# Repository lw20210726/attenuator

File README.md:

# 6GHz attenuator
- 10W celling
- Pick-able tunable 10dB + 20dB fixed: so 0dB - 30dB
- Calculate script included

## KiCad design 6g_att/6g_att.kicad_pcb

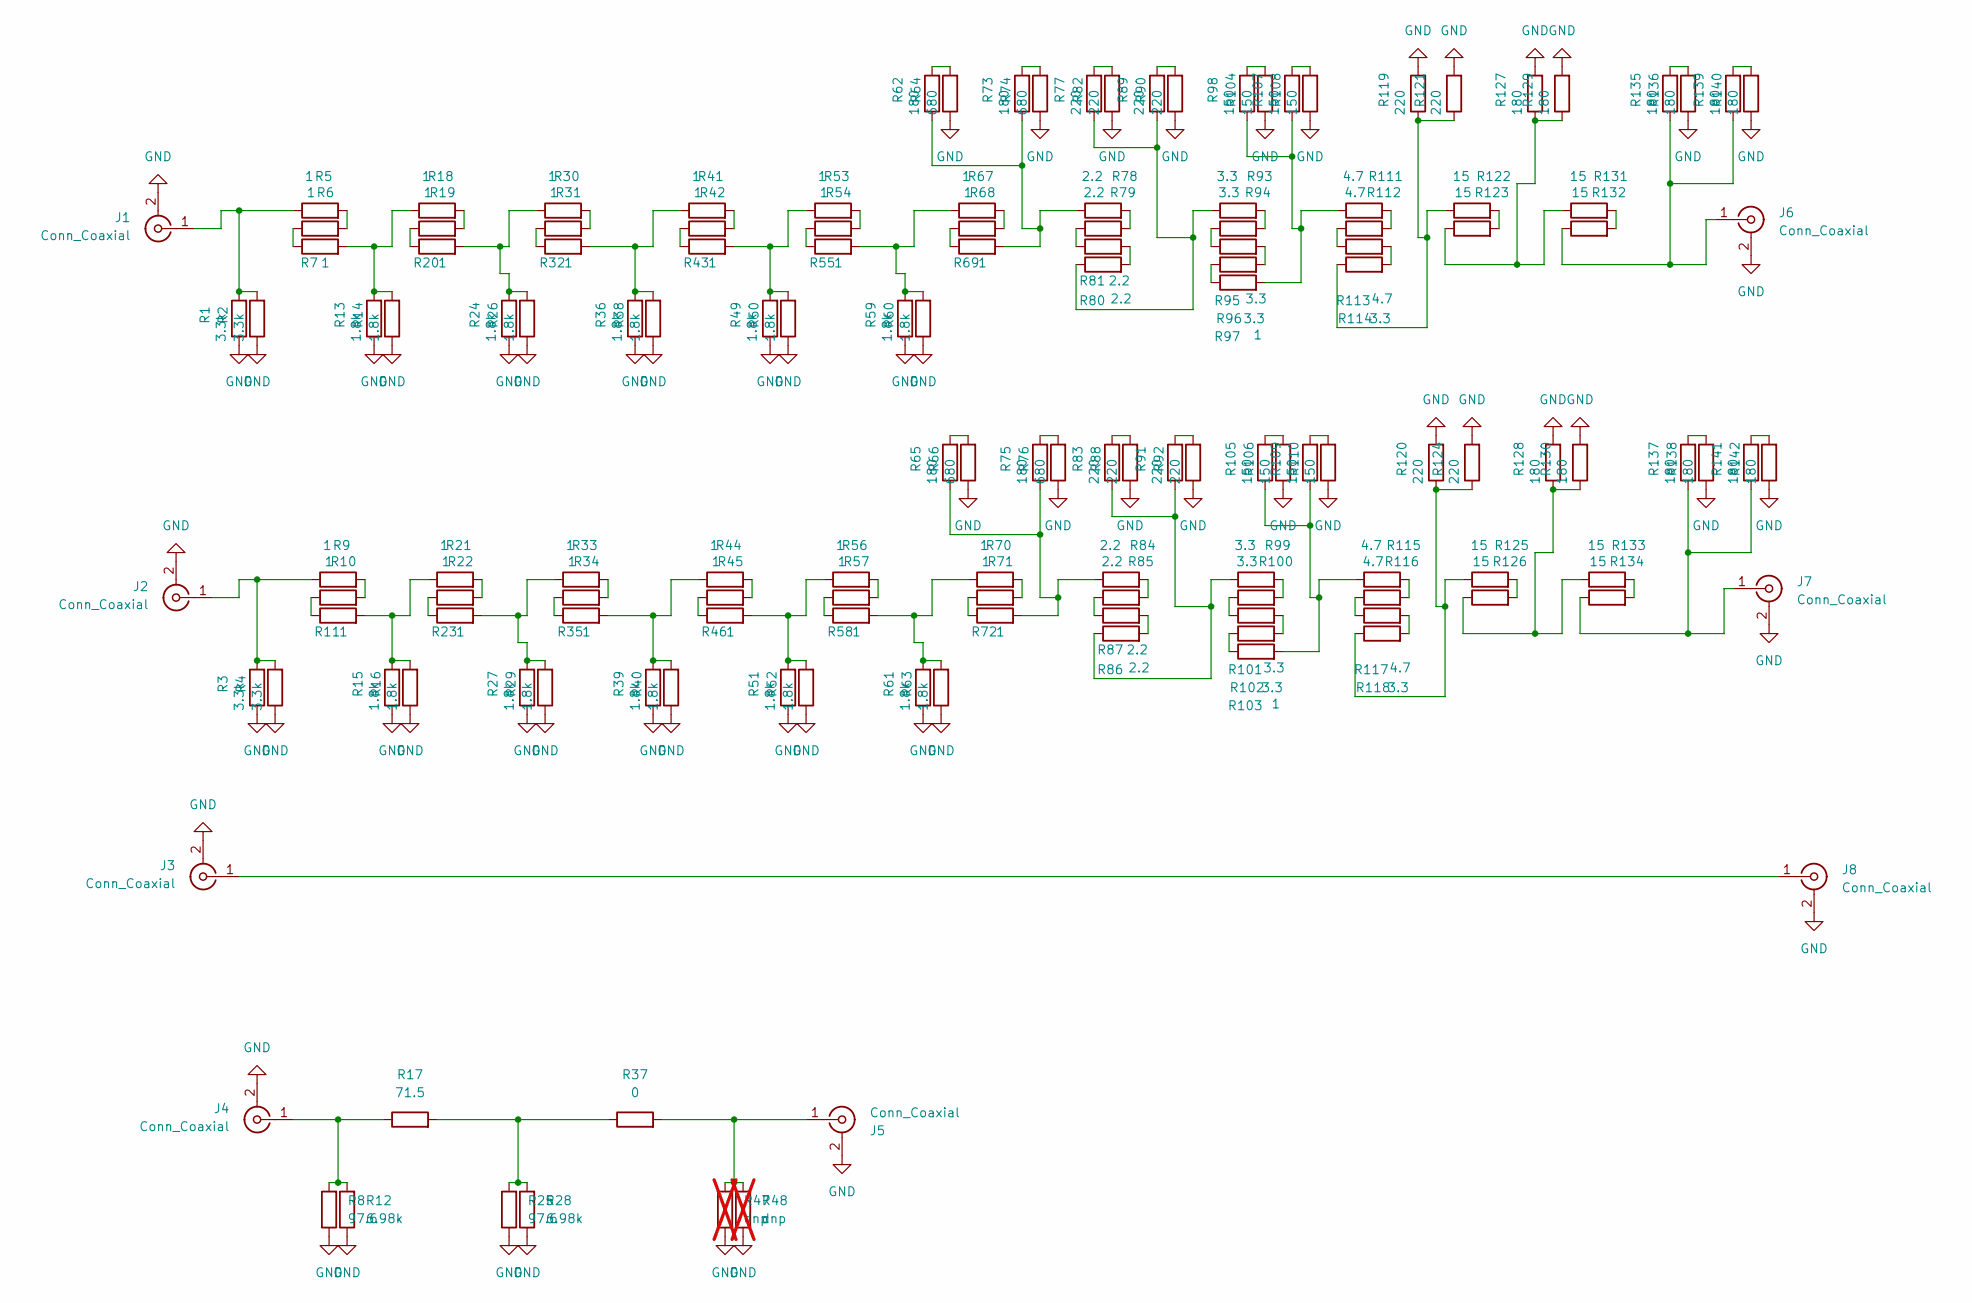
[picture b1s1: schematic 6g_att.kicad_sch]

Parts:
J1, J2, J3, J4, J5, J6, J7, J8: Conn_Coaxial; SMA_Samtec_SMA-J-P-H-ST-EM1_EdgeMount
R1, R2, R3, R4: 3.3k; R_0805_2012Metric
R5, R6, R7, R9, R10, R11, R18, R19, R20, R21, R22, R23, R30, R31, R32, R33, R34, R35, R41, R42, R43, R44, R45, R46, R53, R54, R55, R56, R57, R58, R67, R68, R69, R70, R71, R72, R97, R103: 1; R_0805_2012Metric
R8, R25: 97.6; R_0603_1608Metric
R12, R28: 6.98k; R_0603_1608Metric
R13, R14, R15, R16, R24, R26, R27, R29, R36, R38, R39, R40, R49, R50, R51, R52, R59, R60, R61, R63: 1.8k; R_0805_2012Metric
R17: 71.5; R_0603_1608Metric
R37: 0; R_0603_1608Metric
R47, R48: dnp; R_0603_1608Metric; not fitted
R62, R65, R73, R75, R127, R128, R129, R130, R135, R136, R137, R138, R139, R140, R141, R142: 180; R_0805_2012Metric
R64, R66, R74, R76: 680; R_0805_2012Metric
R77, R82, R83, R88, R89, R90, R91, R92, R119, R120, R121, R124: 220; R_0805_2012Metric
R78, R79, R80, R81, R84, R85, R86, R87: 2.2; R_0805_2012Metric
R93, R94, R95, R96, R99, R100, R101, R102, R114, R118: 3.3; R_0805_2012Metric
R98, R104, R105, R106, R107, R108, R109, R110: 150; R_0805_2012Metric
R111, R112, R113, R115, R116, R117: 4.7; R_0805_2012Metric
R122, R123, R125, R126, R131, R132, R133, R134: 15; R_0805_2012Metric

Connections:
GND: J1.2 (Ext), J2.2 (Ext), J3.2 (Ext), J4.2 (Ext), J5.2 (Ext), J6.2 (Ext), J7.2 (Ext), J8.2 (Ext), R1.1, R2.1, R3.1, R4.1, R8.1, R12.1, R13.1, R14.1, R15.1, R16.1, R24.1, R25.1, R26.1, R27.1, R28.1, R29.1, R36.1, R38.1, R39.1, R40.1, R47.1, R48.1, R49.1, R50.1, R51.1, R52.1, R59.1, R60.1, R61.1, R63.1, R64.1, R66.1, R74.1, R76.1, R82.1, R88.1, R90.1, R92.1, R104.1, R106.1, R108.1, R110.1, R119.2, R120.2, R121.2, R124.2, R127.2, R128.2, R129.2, R130.2, R136.1, R138.1, R140.1, R142.1
unnamed: J1.1 (In), R1.2, R2.2, R5.1
unnamed: J2.1 (In), R3.2, R4.2, R9.1
unnamed: J3.1 (In), J8.1 (In)
unnamed: J4.1 (In), R8.2, R12.2, R17.1
unnamed: J5.1 (In), R37.2, R47.2, R48.2
unnamed: J6.1 (In), R132.1, R135.1, R139.1
unnamed: J7.1 (In), R134.1, R137.1, R141.1
unnamed: R5.2, R6.2
unnamed: R6.1, R7.1
unnamed: R10.1, R11.1
unnamed: R9.2, R10.2
unnamed: R11.2, R15.2, R16.2, R21.1
unnamed: R7.2, R13.2, R14.2, R18.1
unnamed: R17.2, R25.2, R28.2, R37.1
unnamed: R18.2, R19.2
unnamed: R19.1, R20.1
unnamed: R20.2, R24.2, R26.2, R30.1
unnamed: R21.2, R22.2
unnamed: R22.1, R23.1
unnamed: R23.2, R27.2, R29.2, R33.1
unnamed: R30.2, R31.2
unnamed: R31.1, R32.1
unnamed: R32.2, R36.2, R38.2, R41.1
unnamed: R33.2, R34.2
unnamed: R34.1, R35.1
unnamed: R35.2, R39.2, R40.2, R44.1
unnamed: R41.2, R42.2
unnamed: R42.1, R43.1
unnamed: R43.2, R49.2, R50.2, R53.1
unnamed: R44.2, R45.2
unnamed: R45.1, R46.1
unnamed: R46.2, R51.2, R52.2, R56.1
unnamed: R53.2, R54.2
unnamed: R54.1, R55.1
unnamed: R55.2, R59.2, R60.2, R67.1
unnamed: R56.2, R57.2
unnamed: R57.1, R58.1
unnamed: R58.2, R61.2, R63.2, R70.1
unnamed: R62.1, R69.2, R73.1, R78.1
unnamed: R62.2, R64.2
unnamed: R65.1, R72.2, R75.1, R84.1
unnamed: R65.2, R66.2
unnamed: R67.2, R68.2
unnamed: R68.1, R69.1
unnamed: R70.2, R71.2
unnamed: R71.1, R72.1
unnamed: R73.2, R74.2
unnamed: R75.2, R76.2
unnamed: R77.1, R81.1, R89.1, R93.1
unnamed: R77.2, R82.2
unnamed: R78.2, R79.2
unnamed: R79.1, R80.1
unnamed: R80.2, R81.2
unnamed: R83.1, R87.1, R91.1, R99.1
unnamed: R83.2, R88.2
unnamed: R84.2, R85.2
unnamed: R85.1, R86.1
unnamed: R86.2, R87.2
unnamed: R89.2, R90.2
unnamed: R91.2, R92.2
unnamed: R93.2, R94.2
unnamed: R94.1, R95.1
unnamed: R95.2, R96.2
unnamed: R96.1, R97.1
unnamed: R100.1, R101.1
unnamed: R99.2, R100.2
unnamed: R101.2, R102.2
unnamed: R102.1, R103.1
unnamed: R103.2, R105.1, R109.1, R115.1
unnamed: R98.2, R104.2
unnamed: R105.2, R106.2
unnamed: R97.2, R98.1, R107.1, R111.1
unnamed: R107.2, R108.2
unnamed: R109.2, R110.2
unnamed: R111.2, R112.2
unnamed: R112.1, R113.1
unnamed: R113.2, R114.2
unnamed: R114.1, R119.1, R121.1, R122.1
unnamed: R115.2, R116.2
unnamed: R116.1, R117.1
unnamed: R117.2, R118.2
unnamed: R118.1, R120.1, R124.1, R125.1
unnamed: R122.2, R123.2
unnamed: R123.1, R127.1, R129.1, R131.1
unnamed: R125.2, R126.2
unnamed: R126.1, R128.1, R130.1, R133.1
unnamed: R131.2, R132.2
unnamed: R133.2, R134.2
unnamed: R135.2, R136.2
unnamed: R137.2, R138.2
unnamed: R139.2, R140.2
unnamed: R141.2, R142.2

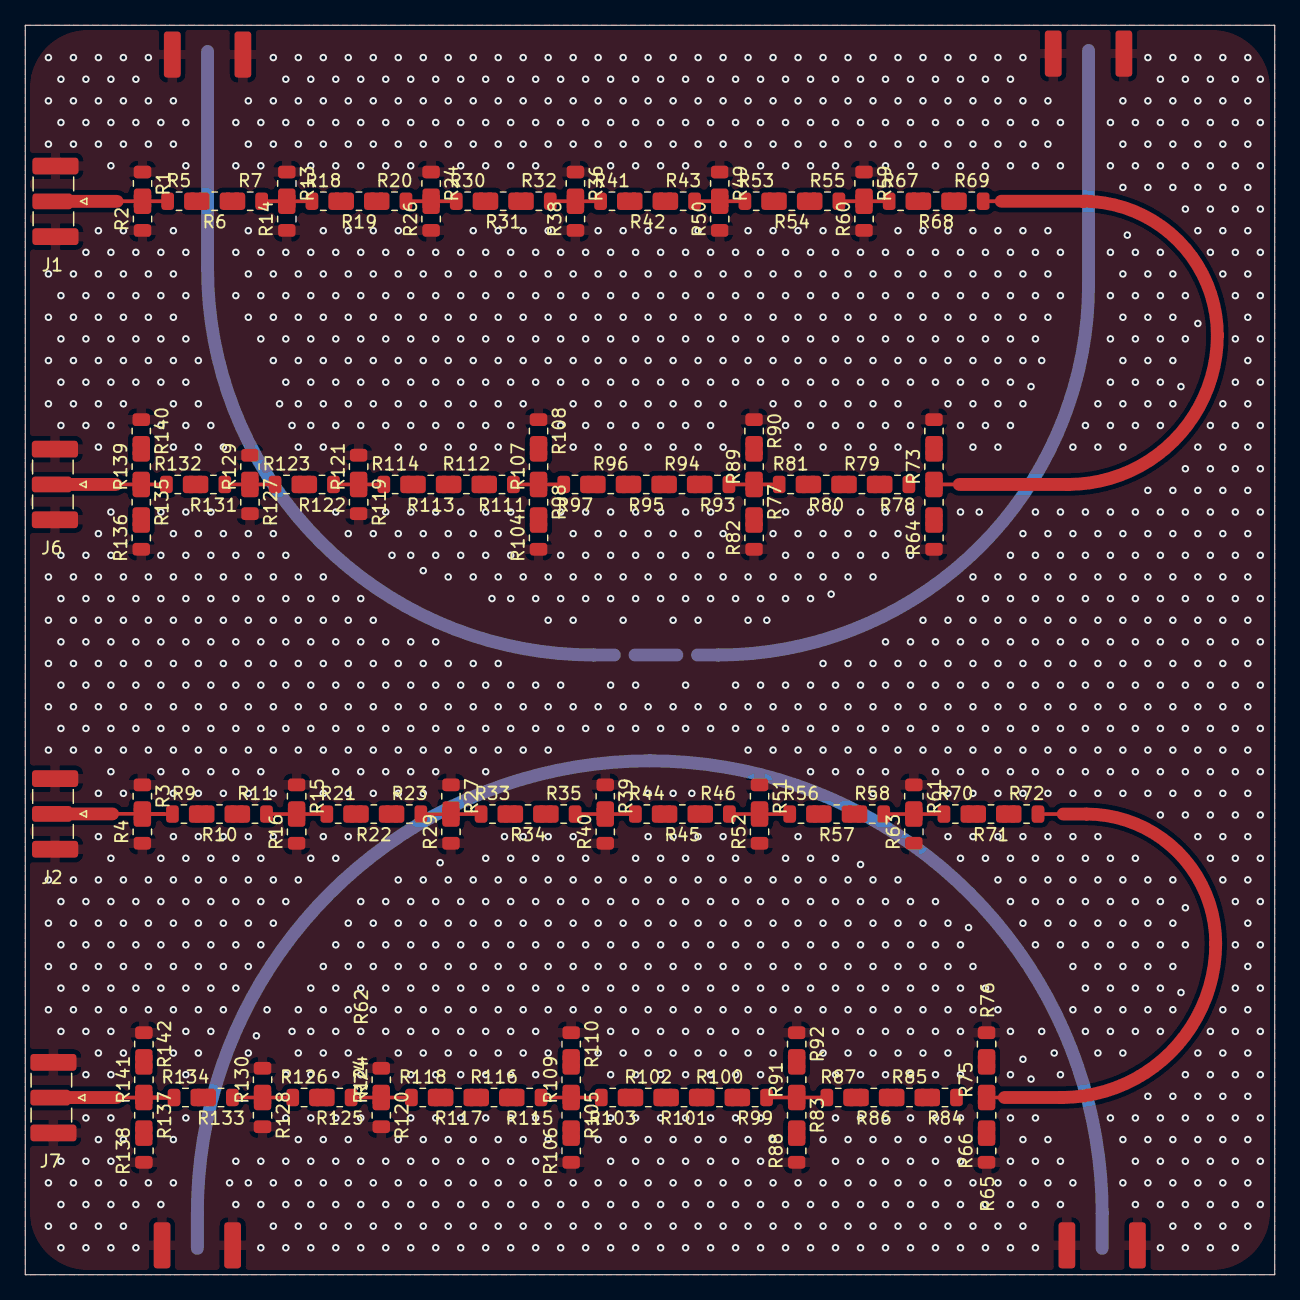
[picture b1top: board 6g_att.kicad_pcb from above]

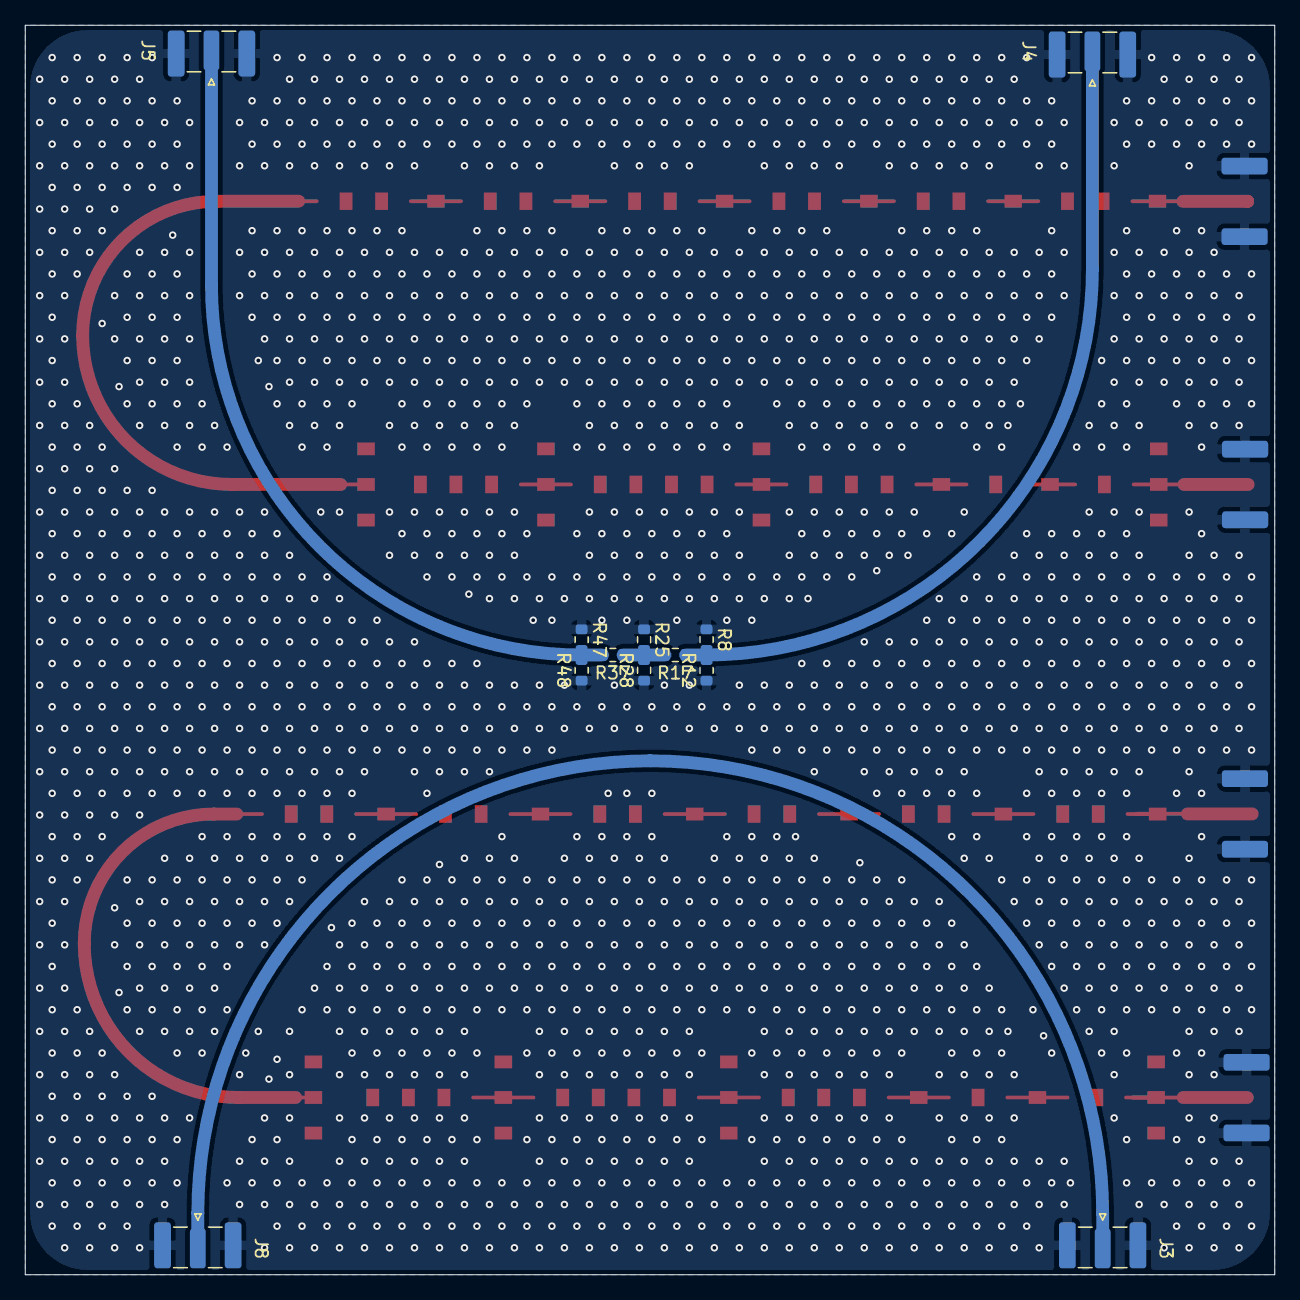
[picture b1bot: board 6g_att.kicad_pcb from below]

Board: 2 copper layers, 100.0 x 100.0 mm, 150 parts (12 on the bottom side), 93 nets.
